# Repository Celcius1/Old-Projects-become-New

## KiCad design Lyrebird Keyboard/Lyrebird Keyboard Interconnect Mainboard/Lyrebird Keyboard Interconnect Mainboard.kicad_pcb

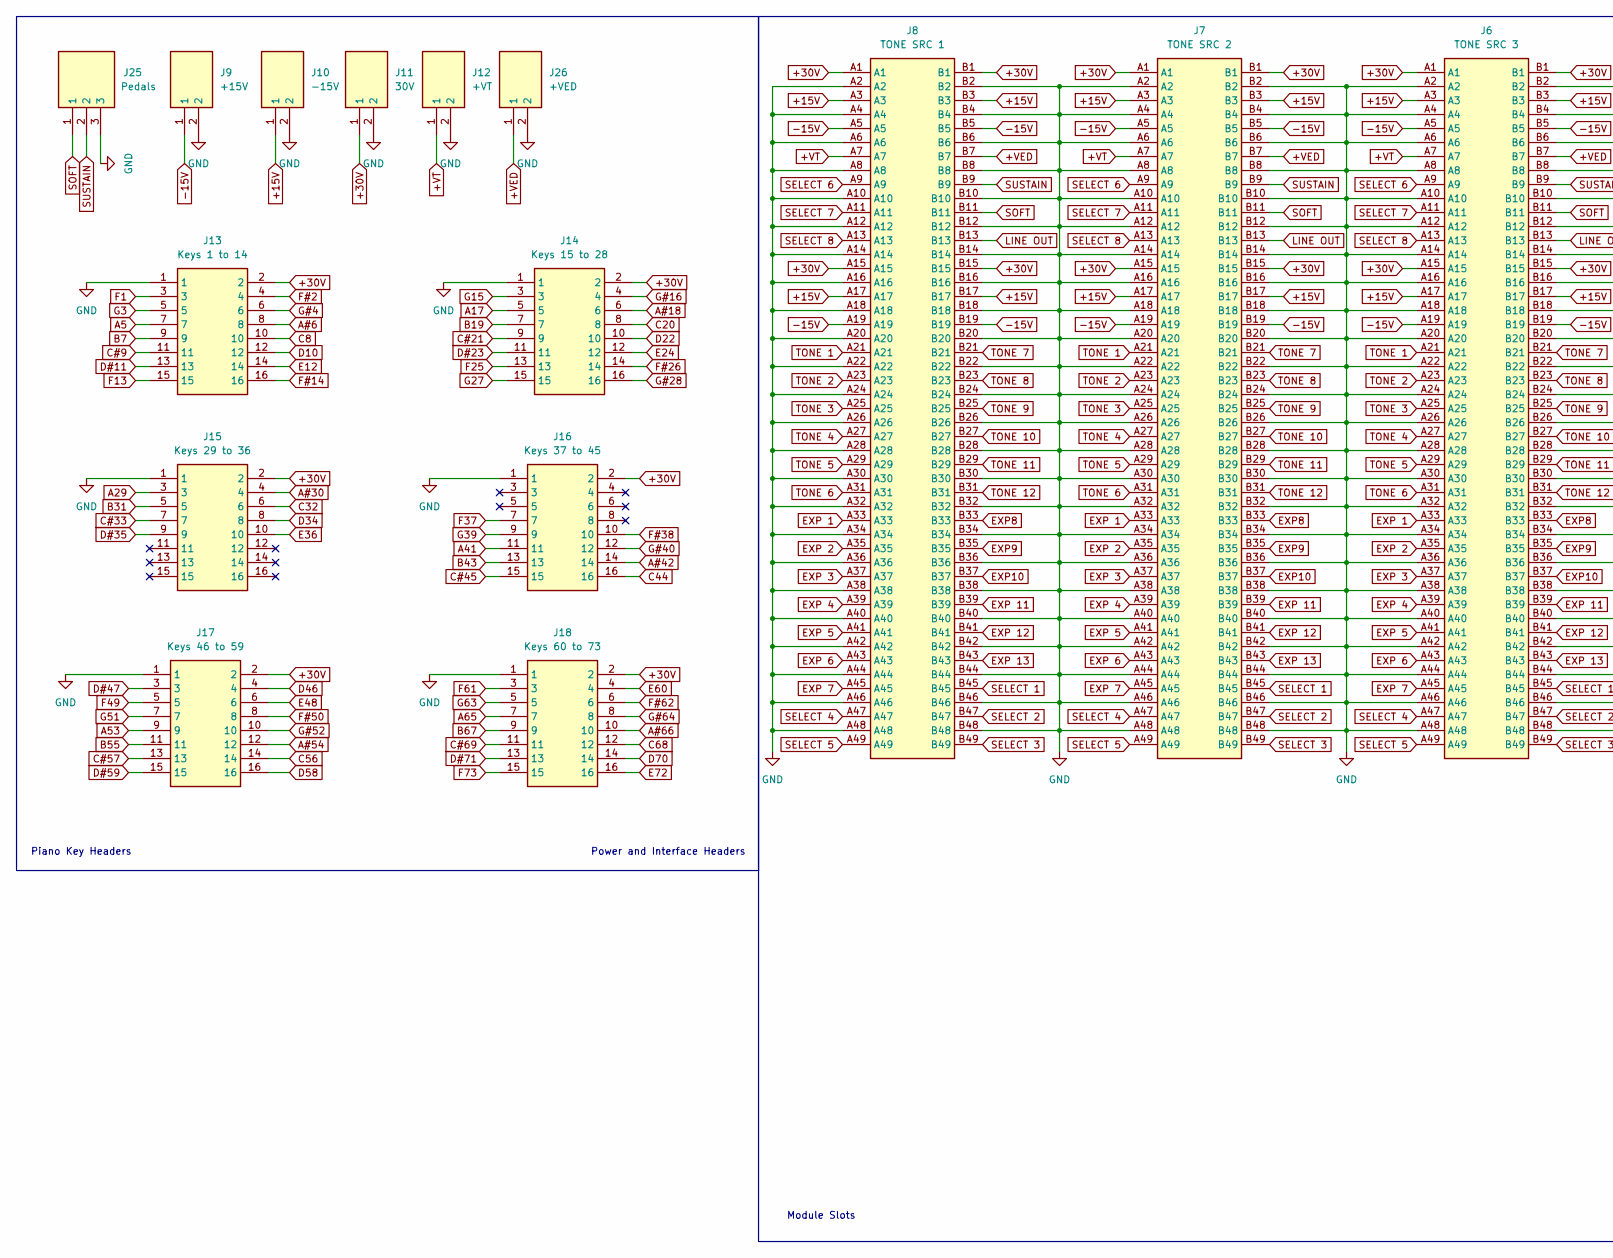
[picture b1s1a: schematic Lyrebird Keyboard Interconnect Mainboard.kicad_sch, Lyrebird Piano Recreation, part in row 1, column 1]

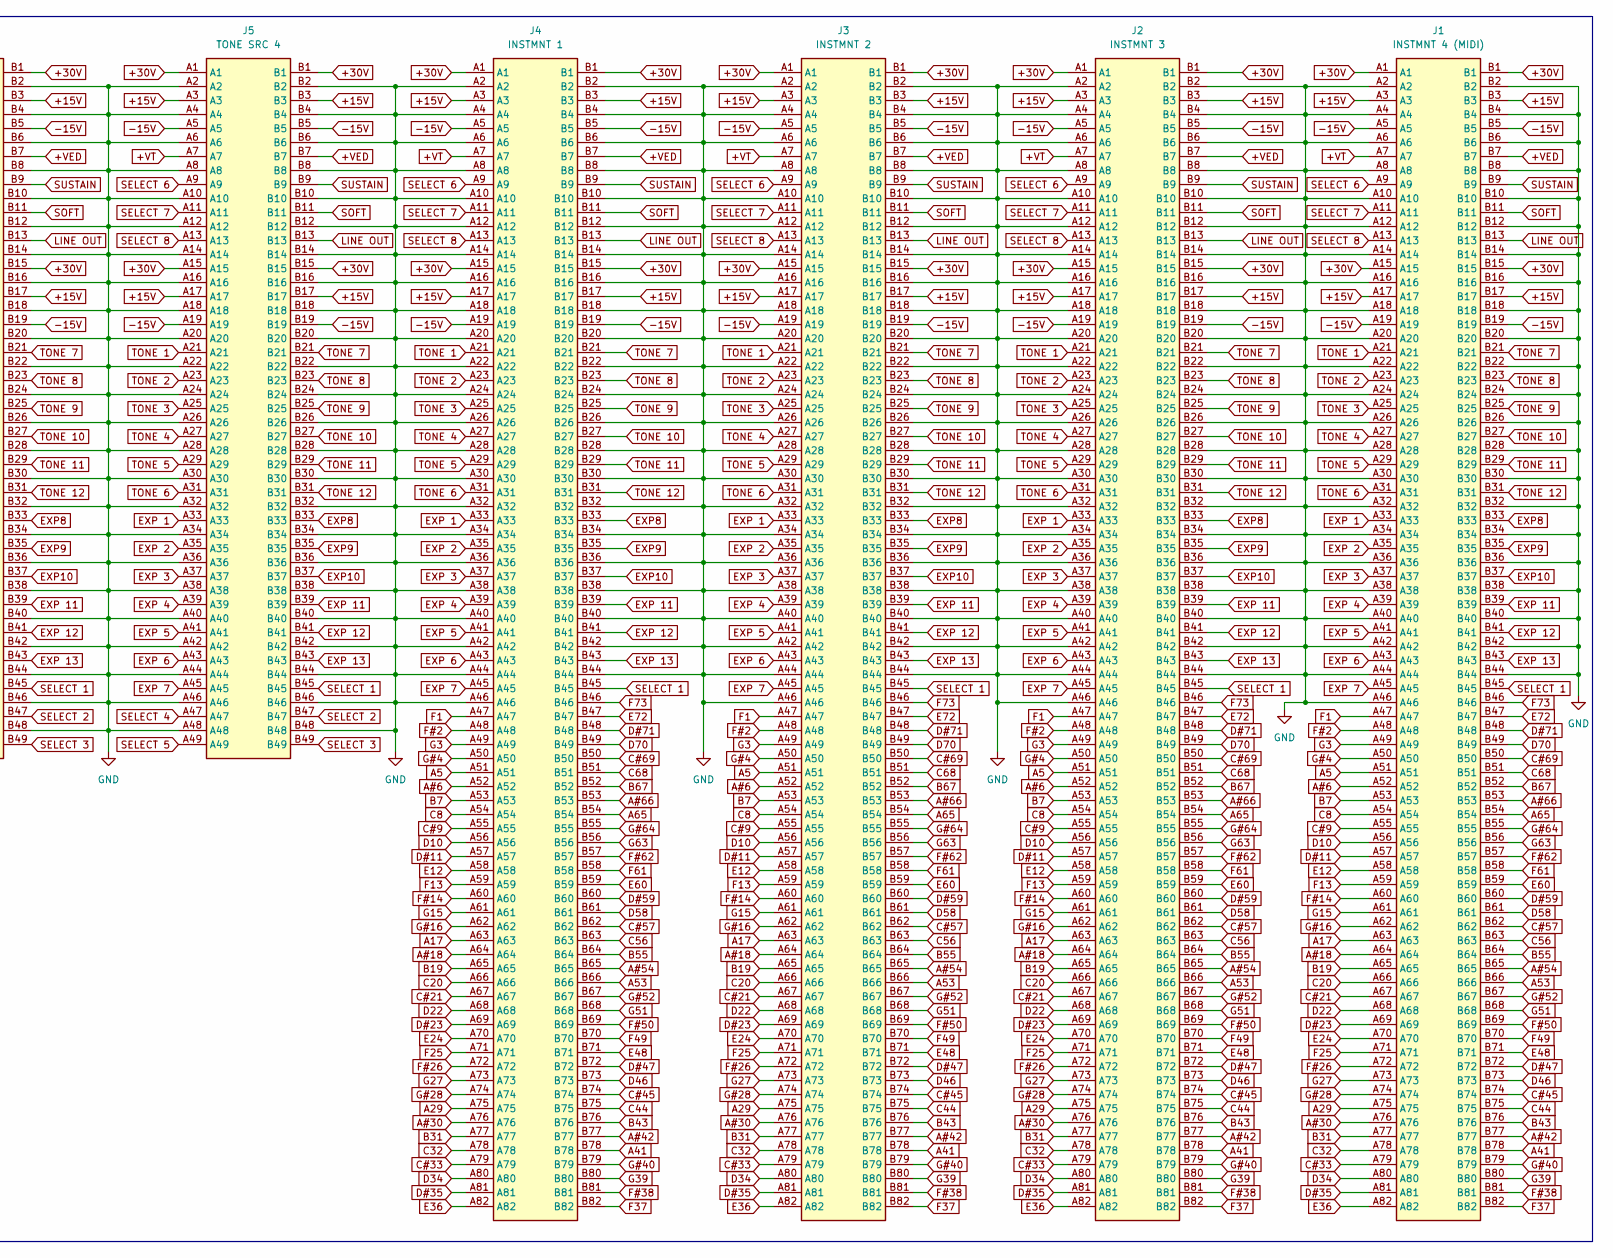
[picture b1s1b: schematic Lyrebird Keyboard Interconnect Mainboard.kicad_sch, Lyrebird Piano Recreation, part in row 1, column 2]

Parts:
J1: INSTMNT 4 (MIDI); 877159306; Manufacturer_Part_Number 87715-9306
J2: INSTMNT 3; 877159306; Manufacturer_Part_Number 87715-9306
J3: INSTMNT 2; 877159306; Manufacturer_Part_Number 87715-9306
J4: INSTMNT 1; 877159306; Manufacturer_Part_Number 87715-9306
J5: TONE SRC 4; 1001878410212TLF; Manufacturer_Part_Number 10018784-10212TLF
J6: TONE SRC 3; 1001878410212TLF; Manufacturer_Part_Number 10018784-10212TLF
J7: TONE SRC 2; 1001878410212TLF; Manufacturer_Part_Number 10018784-10212TLF
J8: TONE SRC 1; 1001878410212TLF; Manufacturer_Part_Number 10018784-10212TLF
J9: +15V; 17761192; Manufacturer_Part_Number 1776119-2
J10: -15V; 17761192; Manufacturer_Part_Number 1776119-2
J11: 30V; 17761192; Manufacturer_Part_Number 1776119-2
J12: +VT; 17761192; Manufacturer_Part_Number 1776119-2
J13: Keys 1 to 14; SHDR16W64P254_2X8_2798X910X910P; Manufacturer_Part_Number MC-254-16-00-ST-DIP
J14: Keys 15 to 28; SHDR16W64P254_2X8_2798X910X910P; Manufacturer_Part_Number MC-254-16-00-ST-DIP
J15: Keys 29 to 36; SHDR16W64P254_2X8_2798X910X910P; Manufacturer_Part_Number MC-254-16-00-ST-DIP
J16: Keys 37 to 45; SHDR16W64P254_2X8_2798X910X910P; Manufacturer_Part_Number MC-254-16-00-ST-DIP
J17: Keys 46 to 59; SHDR16W64P254_2X8_2798X910X910P; Manufacturer_Part_Number MC-254-16-00-ST-DIP
J18: Keys 60 to 73; SHDR16W64P254_2X8_2798X910X910P; Manufacturer_Part_Number MC-254-16-00-ST-DIP
J25: Pedals; CTB05083; Manufacturer_Part_Number CTB0508/3
J26: +VED; 17761192; Manufacturer_Part_Number 1776119-2

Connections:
+15V: J1.A3, J1.A17, J1.B3, J1.B17, J2.A3, J2.A17, J2.B3, J2.B17, J3.A3, J3.A17, J3.B3, J3.B17, J4.A3, J4.A17, J4.B3, J4.B17, J5.A3, J5.A17, J5.B3, J5.B17, J6.A3, J6.A17, J6.B3, J6.B17, J7.A3, J7.A17, J7.B3, J7.B17, J8.A3, J8.A17, J8.B3, J8.B17, J10.1
+30V: J1.A1, J1.A15, J1.B1, J1.B15, J2.A1, J2.A15, J2.B1, J2.B15, J3.A1, J3.A15, J3.B1, J3.B15, J4.A1, J4.A15, J4.B1, J4.B15, J5.A1, J5.A15, J5.B1, J5.B15, J6.A1, J6.A15, J6.B1, J6.B15, J7.A1, J7.A15, J7.B1, J7.B15, J8.A1, J8.A15, J8.B1, J8.B15, J11.1, J13.2, J14.2, J15.2, J16.2, J17.2, J18.2
+VED: J1.B7, J2.B7, J3.B7, J4.B7, J5.B7, J6.B7, J7.B7, J8.B7, J26.1
+VT: J1.A7, J2.A7, J3.A7, J4.A7, J5.A7, J6.A7, J7.A7, J8.A7, J12.1
-15V: J1.A5, J1.A19, J1.B5, J1.B19, J2.A5, J2.A19, J2.B5, J2.B19, J3.A5, J3.A19, J3.B5, J3.B19, J4.A5, J4.A19, J4.B5, J4.B19, J5.A5, J5.A19, J5.B5, J5.B19, J6.A5, J6.A19, J6.B5, J6.B19, J7.A5, J7.A19, J7.B5, J7.B19, J8.A5, J8.A19, J8.B5, J8.B19, J9.1
A5: J1.A51, J2.A51, J3.A51, J4.A51, J13.7
A17: J1.A63, J2.A63, J3.A63, J4.A63, J14.5
A29: J1.A75, J2.A75, J3.A75, J4.A75, J15.3
A41: J1.B78, J2.B78, J3.B78, J4.B78, J16.11
A53: J1.B66, J2.B66, J3.B66, J4.B66, J17.9
A65: J1.B54, J2.B54, J3.B54, J4.B54, J18.7
A#6: J1.A52, J2.A52, J3.A52, J4.A52, J13.8
A#18: J1.A64, J2.A64, J3.A64, J4.A64, J14.6
A#30: J1.A76, J2.A76, J3.A76, J4.A76, J15.4
A#42: J1.B77, J2.B77, J3.B77, J4.B77, J16.14
A#54: J1.B65, J2.B65, J3.B65, J4.B65, J17.12
A#66: J1.B53, J2.B53, J3.B53, J4.B53, J18.10
B7: J1.A53, J2.A53, J3.A53, J4.A53, J13.9
B19: J1.A65, J2.A65, J3.A65, J4.A65, J14.7
B31: J1.A77, J2.A77, J3.A77, J4.A77, J15.5
B43: J1.B76, J2.B76, J3.B76, J4.B76, J16.13
B55: J1.B64, J2.B64, J3.B64, J4.B64, J17.11
B67: J1.B52, J2.B52, J3.B52, J4.B52, J18.9
C8: J1.A54, J2.A54, J3.A54, J4.A54, J13.10
C20: J1.A66, J2.A66, J3.A66, J4.A66, J14.8
C32: J1.A78, J2.A78, J3.A78, J4.A78, J15.6
C44: J1.B75, J2.B75, J3.B75, J4.B75, J16.16
C56: J1.B63, J2.B63, J3.B63, J4.B63, J17.14
C68: J1.B51, J2.B51, J3.B51, J4.B51, J18.12
C#9: J1.A55, J2.A55, J3.A55, J4.A55, J13.11
C#21: J1.A67, J2.A67, J3.A67, J4.A67, J14.9
C#33: J1.A79, J2.A79, J3.A79, J4.A79, J15.7
C#45: J1.B74, J2.B74, J3.B74, J4.B74, J16.15
C#57: J1.B62, J2.B62, J3.B62, J4.B62, J17.13
C#69: J1.B50, J2.B50, J3.B50, J4.B50, J18.11
D10: J1.A56, J2.A56, J3.A56, J4.A56, J13.12
D22: J1.A68, J2.A68, J3.A68, J4.A68, J14.10
D34: J1.A80, J2.A80, J3.A80, J4.A80, J15.8
D46: J1.B73, J2.B73, J3.B73, J4.B73, J17.4
D58: J1.B61, J2.B61, J3.B61, J4.B61, J17.16
D70: J1.B49, J2.B49, J3.B49, J4.B49, J18.14
D#11: J1.A57, J2.A57, J3.A57, J4.A57, J13.13
D#23: J1.A69, J2.A69, J3.A69, J4.A69, J14.11
D#35: J1.A81, J2.A81, J3.A81, J4.A81, J15.9
D#47: J1.B72, J2.B72, J3.B72, J4.B72, J17.3
D#59: J1.B60, J2.B60, J3.B60, J4.B60, J17.15
D#71: J1.B48, J2.B48, J3.B48, J4.B48, J18.13
E12: J1.A58, J2.A58, J3.A58, J4.A58, J13.14
E24: J1.A70, J2.A70, J3.A70, J4.A70, J14.12
E36: J1.A82, J2.A82, J3.A82, J4.A82, J15.10
E48: J1.B71, J2.B71, J3.B71, J4.B71, J17.6
E60: J1.B59, J2.B59, J3.B59, J4.B59, J18.4
E72: J1.B47, J2.B47, J3.B47, J4.B47, J18.16
EXP8: J1.B33, J2.B33, J3.B33, J4.B33, J5.B33, J6.B33, J7.B33, J8.B33
EXP9: J1.B35, J2.B35, J3.B35, J4.B35, J5.B35, J6.B35, J7.B35, J8.B35
EXP10: J1.B37, J2.B37, J3.B37, J4.B37, J5.B37, J6.B37, J7.B37, J8.B37
EXP 1: J1.A33, J2.A33, J3.A33, J4.A33, J5.A33, J6.A33, J7.A33, J8.A33
EXP 2: J1.A35, J2.A35, J3.A35, J4.A35, J5.A35, J6.A35, J7.A35, J8.A35
EXP 3: J1.A37, J2.A37, J3.A37, J4.A37, J5.A37, J6.A37, J7.A37, J8.A37
EXP 4: J1.A39, J2.A39, J3.A39, J4.A39, J5.A39, J6.A39, J7.A39, J8.A39
EXP 5: J1.A41, J2.A41, J3.A41, J4.A41, J5.A41, J6.A41, J7.A41, J8.A41
EXP 6: J1.A43, J2.A43, J3.A43, J4.A43, J5.A43, J6.A43, J7.A43, J8.A43
EXP 7: J1.A45, J2.A45, J3.A45, J4.A45, J5.A45, J6.A45, J7.A45, J8.A45
EXP 11: J1.B39, J2.B39, J3.B39, J4.B39, J5.B39, J6.B39, J7.B39, J8.B39
EXP 12: J1.B41, J2.B41, J3.B41, J4.B41, J5.B41, J6.B41, J7.B41, J8.B41
EXP 13: J1.B43, J2.B43, J3.B43, J4.B43, J5.B43, J6.B43, J7.B43, J8.B43
F1: J1.A47, J2.A47, J3.A47, J4.A47, J13.3
F13: J1.A59, J2.A59, J3.A59, J4.A59, J13.15
F25: J1.A71, J2.A71, J3.A71, J4.A71, J14.13
F37: J1.B82, J2.B82, J3.B82, J4.B82, J16.7
F49: J1.B70, J2.B70, J3.B70, J4.B70, J17.5
F61: J1.B58, J2.B58, J3.B58, J4.B58, J18.3
F73: J1.B46, J2.B46, J3.B46, J4.B46, J18.15
F#2: J1.A48, J2.A48, J3.A48, J4.A48, J13.4
F#14: J1.A60, J2.A60, J3.A60, J4.A60, J13.16
F#26: J1.A72, J2.A72, J3.A72, J4.A72, J14.14
F#38: J1.B81, J2.B81, J3.B81, J4.B81, J16.10
F#50: J1.B69, J2.B69, J3.B69, J4.B69, J17.8
F#62: J1.B57, J2.B57, J3.B57, J4.B57, J18.6
G3: J1.A49, J2.A49, J3.A49, J4.A49, J13.5
G15: J1.A61, J2.A61, J3.A61, J4.A61, J14.3
G27: J1.A73, J2.A73, J3.A73, J4.A73, J14.15
G39: J1.B80, J2.B80, J3.B80, J4.B80, J16.9
G51: J1.B68, J2.B68, J3.B68, J4.B68, J17.7
G63: J1.B56, J2.B56, J3.B56, J4.B56, J18.5
G#4: J1.A50, J2.A50, J3.A50, J4.A50, J13.6
G#16: J1.A62, J2.A62, J3.A62, J4.A62, J14.4
G#28: J1.A74, J2.A74, J3.A74, J4.A74, J14.16
G#40: J1.B79, J2.B79, J3.B79, J4.B79, J16.12
G#52: J1.B67, J2.B67, J3.B67, J4.B67, J17.10
G#64: J1.B55, J2.B55, J3.B55, J4.B55, J18.8
GND: J1.A2, J1.A4, J1.A6, J1.A8, J1.A10, J1.A12, J1.A14, J1.A16, J1.A18, J1.A20, J1.A22, J1.A24, J1.A26, J1.A28, J1.A30, J1.A32, J1.A34, J1.A36, J1.A38, J1.A40, J1.A42, J1.A44, J1.A46, J1.B2, J1.B4, J1.B6, J1.B8, J1.B10, J1.B12, J1.B14, J1.B16, J1.B18, J1.B20, J1.B22, J1.B24, J1.B26, J1.B28, J1.B30, J1.B32, J1.B34, J1.B36, J1.B38, J1.B40, J1.B42, J1.B44, J2.A2, J2.A4, J2.A6, J2.A8, J2.A10, J2.A12, J2.A14, J2.A16, J2.A18, J2.A20, J2.A22, J2.A24, J2.A26, J2.A28, J2.A30, J2.A32, J2.A34, J2.A36, J2.A38, J2.A40, J2.A42, J2.A44, J2.A46, J2.B2, J2.B4, J2.B6, J2.B8, J2.B10, J2.B12, J2.B14, J2.B16, J2.B18, J2.B20, J2.B22, J2.B24, J2.B26, J2.B28, J2.B30, J2.B32, J2.B34, J2.B36, J2.B38, J2.B40, J2.B42, J2.B44, J3.A2, J3.A4, J3.A6, J3.A8, J3.A10, J3.A12, J3.A14, J3.A16, J3.A18, J3.A20, J3.A22, J3.A24, J3.A26, J3.A28, J3.A30, J3.A32, J3.A34, J3.A36, J3.A38, J3.A40, J3.A42, J3.A44, J3.A46, J3.B2, J3.B4, J3.B6, J3.B8, J3.B10, J3.B12, J3.B14, J3.B16, J3.B18, J3.B20, J3.B22, J3.B24, J3.B26, J3.B28, J3.B30, J3.B32, J3.B34, J3.B36, J3.B38, J3.B40, J3.B42, J3.B44, J4.A2, J4.A4, J4.A6, J4.A8, J4.A10, J4.A12, J4.A14, J4.A16, J4.A18, J4.A20, J4.A22, J4.A24, J4.A26, J4.A28, J4.A30, J4.A32, J4.A34, J4.A36, J4.A38, J4.A40, J4.A42, J4.A44, J4.A46, J4.B2, J4.B4, J4.B6, J4.B8, J4.B10, J4.B12, J4.B14, J4.B16, J4.B18, J4.B20, J4.B22, J4.B24, J4.B26, J4.B28, J4.B30, J4.B32, J4.B34, J4.B36, J4.B38, J4.B40, J4.B42, J4.B44, J5.A2, J5.A4, J5.A6, J5.A8, J5.A10, J5.A12, J5.A14, J5.A16, J5.A18, J5.A20, J5.A22, J5.A24, J5.A26, J5.A28, J5.A30, J5.A32, J5.A34, J5.A36, J5.A38, J5.A40, J5.A42, J5.A44, J5.A46, J5.A48, J5.B2, J5.B4, J5.B6, J5.B8, J5.B10, J5.B12, J5.B14, J5.B16, J5.B18, J5.B20, J5.B22, J5.B24, J5.B26, J5.B28, J5.B30, J5.B32, J5.B34, J5.B36, J5.B38, J5.B40, J5.B42, J5.B44, J5.B46, J5.B48, J6.A2, J6.A4, J6.A6, J6.A8, J6.A10, J6.A12, J6.A14, J6.A16, J6.A18, J6.A20, J6.A22, J6.A24, J6.A26, J6.A28, J6.A30, J6.A32, J6.A34, J6.A36, J6.A38, J6.A40, J6.A42, J6.A44, J6.A46, J6.A48, J6.B2, J6.B4, J6.B6, J6.B8, J6.B10, J6.B12, J6.B14, J6.B16, J6.B18, J6.B20, J6.B22, J6.B24, J6.B26, J6.B28, J6.B30, J6.B32, J6.B34, J6.B36, J6.B38, J6.B40, J6.B42, J6.B44, J6.B46, J6.B48, J7.A2, J7.A4, J7.A6, J7.A8, J7.A10, J7.A12, J7.A14, J7.A16, J7.A18, J7.A20, J7.A22, J7.A24, J7.A26, J7.A28, J7.A30, J7.A32, J7.A34, J7.A36, J7.A38, J7.A40, J7.A42, J7.A44, J7.A46, J7.A48, J7.B2, J7.B4, J7.B6, J7.B8, J7.B10, J7.B12, J7.B14, J7.B16, J7.B18, J7.B20, J7.B22, J7.B24, J7.B26, J7.B28, J7.B30, J7.B32, J7.B34, J7.B36, J7.B38, J7.B40, J7.B42, J7.B44, J7.B46, J7.B48, J8.A2, J8.A4, J8.A6, J8.A8, J8.A10, J8.A12, J8.A14, J8.A16, J8.A18, J8.A20, J8.A22, J8.A24, J8.A26, J8.A28, J8.A30, J8.A32, J8.A34, J8.A36, J8.A38, J8.A40, J8.A42, J8.A44, J8.A46, J8.A48, J8.B2, J8.B4, J8.B6, J8.B8, J8.B10, J8.B12, J8.B14, J8.B16, J8.B18, J8.B20, J8.B22, J8.B24, J8.B26, J8.B28, J8.B30, J8.B32, J8.B34, J8.B36, J8.B38, J8.B40, J8.B42, J8.B44, J8.B46, J8.B48, J9.2, J10.2, J11.2, J12.2, J13.1, J14.1, J15.1, J16.1, J17.1, J18.1, J25.3, J26.2
LINE OUT: J1.B13, J2.B13, J3.B13, J4.B13, J5.B13, J6.B13, J7.B13, J8.B13
SELECT 1: J1.B45, J2.B45, J3.B45, J4.B45, J5.B45, J6.B45, J7.B45, J8.B45
SELECT 2: J5.B47, J6.B47, J7.B47, J8.B47
SELECT 3: J5.B49, J6.B49, J7.B49, J8.B49
SELECT 4: J5.A47, J6.A47, J7.A47, J8.A47
SELECT 5: J5.A49, J6.A49, J7.A49, J8.A49
SELECT 6: J1.A9, J2.A9, J3.A9, J4.A9, J5.A9, J6.A9, J7.A9, J8.A9
SELECT 7: J1.A11, J2.A11, J3.A11, J4.A11, J5.A11, J6.A11, J7.A11, J8.A11
SELECT 8: J1.A13, J2.A13, J3.A13, J4.A13, J5.A13, J6.A13, J7.A13, J8.A13
SOFT: J1.B11, J2.B11, J3.B11, J4.B11, J5.B11, J6.B11, J7.B11, J8.B11, J25.1
SUSTAIN: J1.B9, J2.B9, J3.B9, J4.B9, J5.B9, J6.B9, J7.B9, J8.B9, J25.2
TONE 1: J1.A21, J2.A21, J3.A21, J4.A21, J5.A21, J6.A21, J7.A21, J8.A21
TONE 2: J1.A23, J2.A23, J3.A23, J4.A23, J5.A23, J6.A23, J7.A23, J8.A23
TONE 3: J1.A25, J2.A25, J3.A25, J4.A25, J5.A25, J6.A25, J7.A25, J8.A25
TONE 4: J1.A27, J2.A27, J3.A27, J4.A27, J5.A27, J6.A27, J7.A27, J8.A27
TONE 5: J1.A29, J2.A29, J3.A29, J4.A29, J5.A29, J6.A29, J7.A29, J8.A29
TONE 6: J1.A31, J2.A31, J3.A31, J4.A31, J5.A31, J6.A31, J7.A31, J8.A31
TONE 7: J1.B21, J2.B21, J3.B21, J4.B21, J5.B21, J6.B21, J7.B21, J8.B21
TONE 8: J1.B23, J2.B23, J3.B23, J4.B23, J5.B23, J6.B23, J7.B23, J8.B23
TONE 9: J1.B25, J2.B25, J3.B25, J4.B25, J5.B25, J6.B25, J7.B25, J8.B25
TONE 10: J1.B27, J2.B27, J3.B27, J4.B27, J5.B27, J6.B27, J7.B27, J8.B27
TONE 11: J1.B29, J2.B29, J3.B29, J4.B29, J5.B29, J6.B29, J7.B29, J8.B29
TONE 12: J1.B31, J2.B31, J3.B31, J4.B31, J5.B31, J6.B31, J7.B31, J8.B31

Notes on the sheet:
Piano Key Headers
Power and Interface Headers
Module Slots

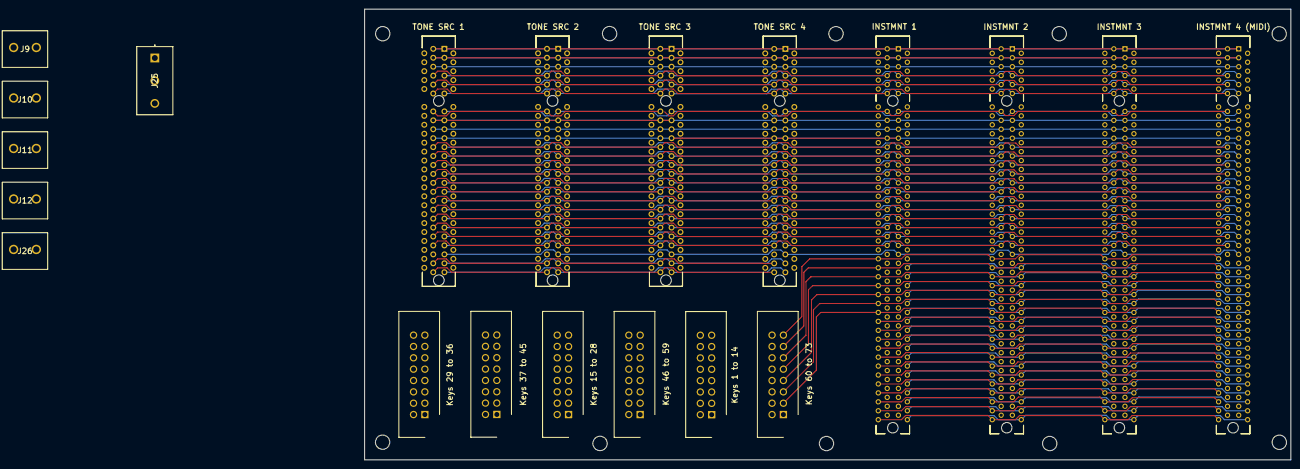
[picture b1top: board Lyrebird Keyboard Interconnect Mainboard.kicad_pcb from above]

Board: 4 copper layers, 207.3 x 100.9 mm, 20 parts (0 on the bottom side), 115 nets.

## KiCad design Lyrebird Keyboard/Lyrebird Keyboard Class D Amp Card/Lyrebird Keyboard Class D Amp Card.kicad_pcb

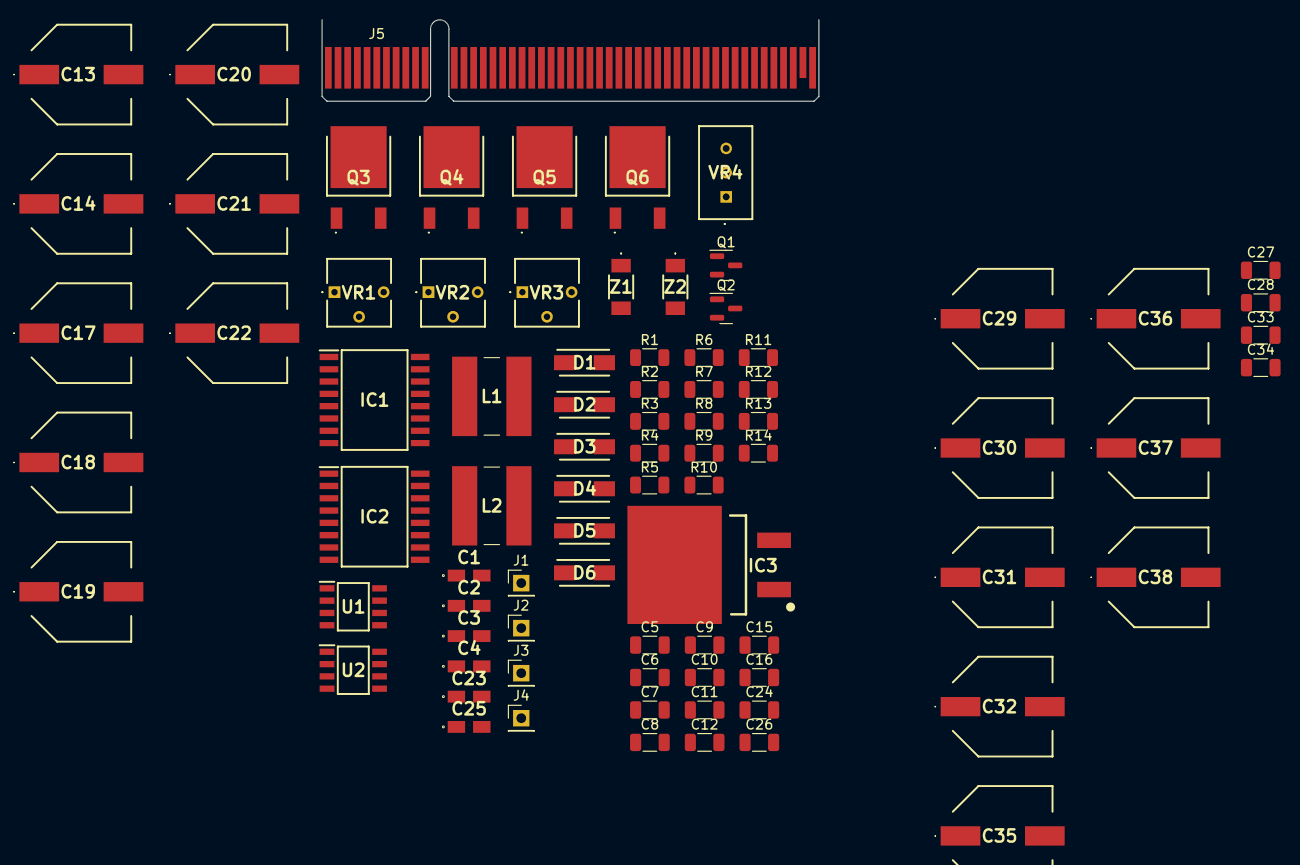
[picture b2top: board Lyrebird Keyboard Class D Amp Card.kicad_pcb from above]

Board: 2 copper layers, 82 parts (0 on the bottom side), 36 nets, no tracks yet.

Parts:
C1, C2, C3, C4, C23, C25: T491A225K016AT; T491A
C5, C6, C11, C12, C28, C34: 220nF; C_1206_3216Metric
C7, C8: 22uF; C_1206_3216Metric
C9, C10, C27, C33: 100nF; C_1206_3216Metric
C13, C14, C17, C18, C19, C20, C21, C22, C29, C30, C31, C32, C35, C36, C37, C38: EEEFK1H221P; EEE0JA152UAP
C15: 390nF; C_1206_3216Metric
C16: 5.6uF; C_1206_3216Metric
C24: 68nF; C_1206_3216Metric
C26: 1nF; C_1206_3216Metric
D1, D2, D3, D4, D5, D6: US1M-E3_5AT; DIOM5127X229N
IC1, IC2: IR2113SPBF; SOIC127P1032X265-16N
IC3: L7805ACD2T-TR; D2PAK-STB35NF10T4
J1: Bias Test Point 1; PinHeader_1x01_P2.54mm_Vertical
J2: Bias Test Point 2; PinHeader_1x01_P2.54mm_Vertical
J3: Square Test; PinHeader_1x01_P2.54mm_Vertical
J4: Triangle Test; PinHeader_1x01_P2.54mm_Vertical
J5: Edge Connector; BUS_PCIexpress_x8
L1, L2: SRN8040-220M; SRN8040220M
Q1, Q2: BC848; SOT-23
Q3, Q4, Q5, Q6: IRFR2905ZTRPBF
R1, R2, R3, R4, R5, R6, R11: 10k; R_1206_3216Metric
R7, R8, R9, R10: 10R; R_1206_3216Metric
R12, R13: 100k; R_1206_3216Metric
R14: 5k1; R_1206_3216Metric
U1: SOIC127P600X175-8N
U2: LM358; SOIC127P600X175-8N
VR1, VR2, VR3: T73YP103KT20
VR4: CT-9EW104; CT9EW104
Z1, Z2: PDZVTFTR4.7B; PDZVTFTR47B

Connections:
+5V: C1.1 (+), C2.1 (+), C3.1 (+), C4.1 (+), C23.1 (+), C25.1 (+), IC1.11 (VDD), IC2.11 (VDD), IC3.3 (OUTPUT), R3.1, R4.1, R5.2, R6.2, U1.8 (Vdd), U2.8 (V+), VR2.3 (CW), VR3.3 (CW)
+15V: C9.2, C10.2, C11.2, C12.2, C13.1 (+), C14.1 (+), C17.1 (+), C18.1 (+), C19.1 (+), C20.1 (+), C21.1 (+), C22.1 (+), D1.2 (A), D2.2 (A), IC1.3 (VCC), IC2.3 (VCC), IC3.1 (INPUT), J5.A3, J5.A17, J5.B3, J5.B17, Q3.2 (D), Q5.2 (D)
-15V: C27.1, C28.1, C29.2 (-), C30.2 (-), C31.2 (-), C32.2 (-), C33.1, C34.1, C35.2 (-), C36.2 (-), C37.2 (-), C38.2 (-), J5.A5, J5.A19, J5.B5, J5.B19, Q4.3 (S), Q6.3 (S)
AMP OUT: C15.2, L1.2
GND: C1.2 (-), C2.2 (-), C3.2 (-), C4.2 (-), C9.1, C10.1, C11.1, C12.1, C13.2 (-), C14.2 (-), C15.1, C16.1, C17.2 (-), C18.2 (-), C19.2 (-), C20.2 (-), C21.2 (-), C22.2 (-), C23.2 (-), C24.1, C25.2 (-), C27.2, C28.2, C29.1 (+), C30.1 (+), C31.1 (+), C32.1 (+), C33.2, C34.2, C35.1 (+), C36.1 (+), C37.1 (+), C38.1 (+), IC1.13 (SD), IC2.13 (SD), IC3.4 (GND), J5.A2, J5.A4, J5.A6, J5.A8, J5.A10, J5.A12, J5.A14, J5.A16, J5.A18, J5.A20, J5.A32, J5.A34, J5.A36, J5.A38, J5.A40, J5.A42, J5.A44, J5.A46, J5.A48, J5.B2, J5.B4, J5.B6, J5.B8, J5.B10, J5.B12, J5.B14, J5.B16, J5.B18, J5.B20, J5.B32, J5.B34, J5.B36, J5.B38, J5.B40, J5.B42, J5.B44, J5.B46, J5.B48, Q1.2 (E), Q2.2 (E), U1.4 (Vss), U2.2 (-), U2.4 (V-), U2.5 (+), VR2.1 (CCW), VR3.1 (CCW), Z1.2 (A)
HIN1: IC1.12 (HIN), R1.1, R6.1, U1.7
HIN2: IC2.12 (HIN), R2.1, R5.1, U1.1
HO1: D5.1 (K), IC1.8 (HO), R9.2
HO2: D3.1 (K), IC2.8 (HO), R7.2
LINE INV: IC2.14 (LIN), Q2.3 (C), R4.2
LINE OUT: J5.B13, VR1.3 (CW)
LO1: D6.1 (K), IC1.1 (LO), R10.2
LO2: D4.1 (K), IC2.1 (LO), R8.2
unnamed: D3.2 (A), Q3.1 (G), R7.1
unnamed: D4.2 (A), Q4.1 (G), R8.1
unnamed: D5.2 (A), Q5.1 (G), R9.1
unnamed: D6.2 (A), Q6.1 (G), R10.1
unnamed: J1.1, U1.2 (-), VR1.1 (CCW), VR2.2 (WIPER)
unnamed: J3.1, R13.1, R14.2, VR4.1 (CCW), Z2.2 (A)
unnamed: Q1.1 (B), R1.2
unnamed: Q2.1 (B), R2.2
unnamed: R14.1, U2.1
unnamed: C24.2, R11.1, U1.6 (-)
unnamed: R12.2, R13.2, U2.3 (+)
unnamed: C26.1, U2.6 (-), VR4.2 (WIPER)
unnamed: Z1.1 (K), Z2.1 (K)
SUB IN: J2.1, R11.2, VR1.2 (WIPER), VR3.2 (WIPER)
SUB INV: IC1.14 (LIN), Q1.3 (C), R3.2
SUBWOOFER: C16.2, L2.2
TRI WAVE OUT: C26.2, J4.1, R12.1, U1.3 (+), U1.5 (+), U2.7
VB1: C6.1, C8.2, D2.1 (K), IC1.7 (VB)
VB2: C5.1, C7.2, D1.1 (K), IC2.7 (VB)
VS1: C6.2, C8.1, IC1.6 (VS), L2.1, Q5.3 (S), Q6.2 (D)
VS2: C5.2, C7.1, IC2.6 (VS), L1.1, Q3.3 (S), Q4.2 (D)
VSS1: IC1.2 (COM), IC1.15 (VSS)
VSS2: IC2.2 (COM), IC2.15 (VSS)

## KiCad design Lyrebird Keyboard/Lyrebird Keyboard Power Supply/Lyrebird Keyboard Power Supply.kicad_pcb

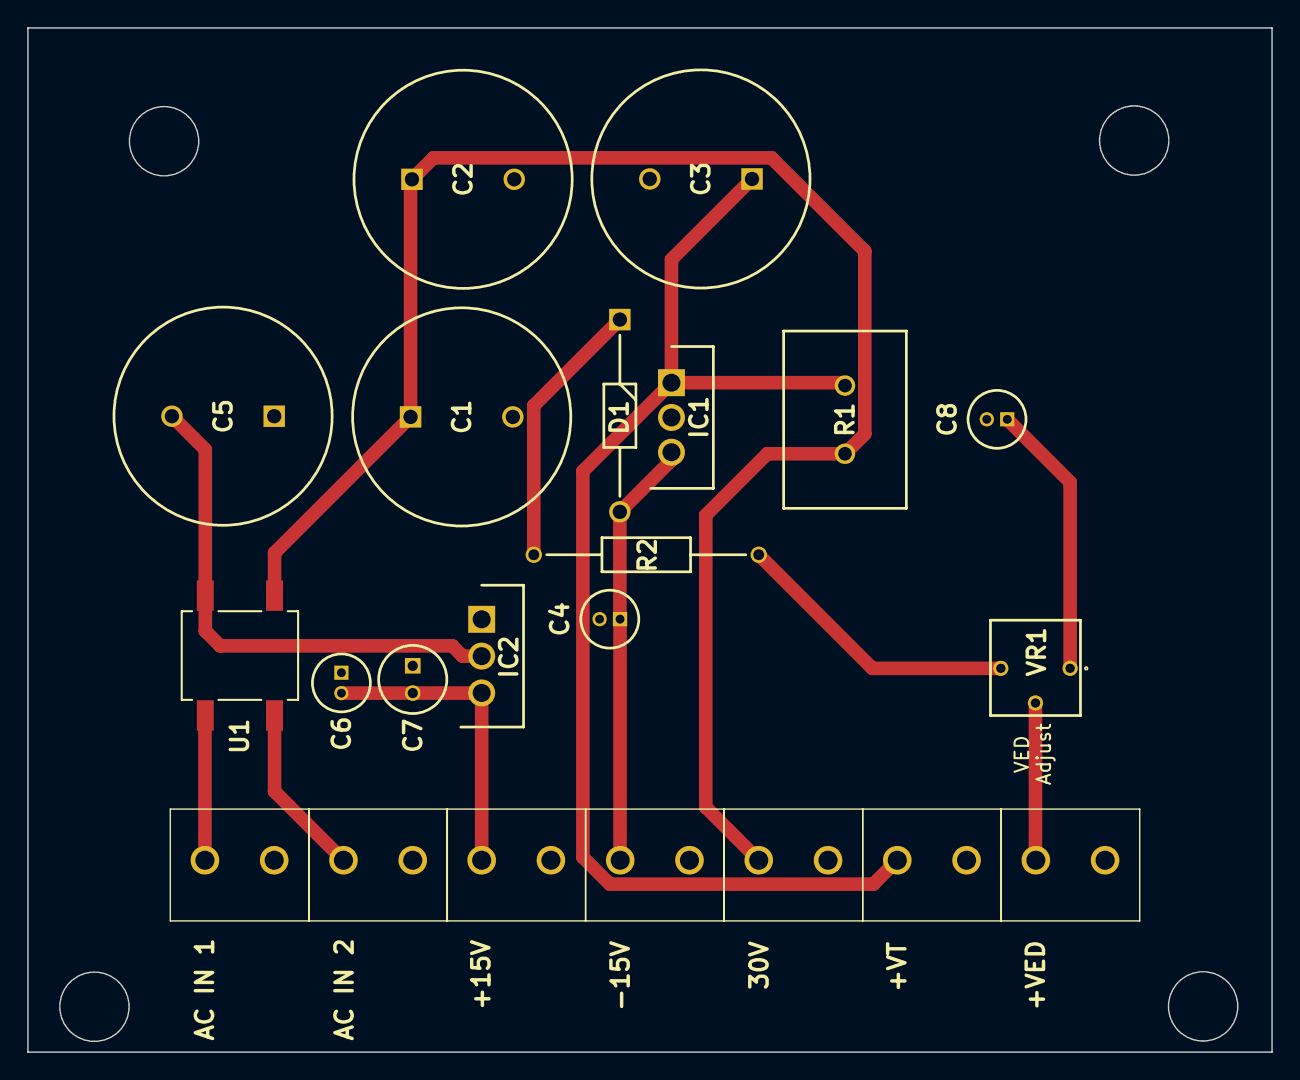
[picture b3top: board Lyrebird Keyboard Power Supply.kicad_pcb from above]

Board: 2 copper layers, 91.2 x 75.1 mm, 22 parts (0 on the bottom side), 12 nets.

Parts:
C1, C2, C3, C5: ECA1HHG222; CAPPRD750W85D1600H3350
C4, C6, C8: MCMHR50V104M4X7; CAPPRD150W47D425H800
C7: EEUFC1H4R7; CAPPRD200W55D500H1250
D1: 1N4002G; DIOAD1405W86L465D235
IC1: L78S15CV; TO255P460X1020X2008-3P
IC2: L7915CV; TO270P460X1020X2008-3P
J1: AC IN 1; 17761192
J2: AC IN 2; 17761192
J3: +15V; 17761192
J4: -15V; 17761192
J5: 30V; 17761192
J6: +VT; 17761192
J7: +VED; 17761192
R1: SQMR54K7J
R2: MRS25000C1801FCT00; RESAD1650W60L650D250
U1: DF06S; SOT508P985X260-4N
VR1: 3362P-1-102LF; 3362P_1

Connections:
+15V: C4.1 (+), D1.2 (A), IC1.3 (OUTPUT), J4.1
+30V: C1.1 (+), C2.1 (+), J5.1, R1.1, U1.1 (OUT+)
+VED: J7.1, VR1.2 (WIPER)
+VT: C3.1 (+), IC1.1 (INPUT), J6.1, R1.2
-15V: C6.2 (-), C7.2 (-), IC2.3 (OUT), J3.1
AC1: J1.1, U1.3 (AC)
AC2: J2.1, U1.4 (AC_2)
GND: C1.2 (-), C2.2 (-), C3.2 (-), C4.2 (-), C5.1 (+), C6.1 (+), C7.1 (+), C8.2 (-), IC1.2 (GROUND), IC2.1 (GND), J1.2, J2.2, J3.2, J4.2, J5.2, J6.2, J7.2
unnamed: C5.2 (-), IC2.2 (IN), U1.2 (OUT-)
unnamed: C8.1 (+), VR1.1 (CCW)
unnamed: D1.1 (K), R2.1
unnamed: R2.2, VR1.3 (CW)

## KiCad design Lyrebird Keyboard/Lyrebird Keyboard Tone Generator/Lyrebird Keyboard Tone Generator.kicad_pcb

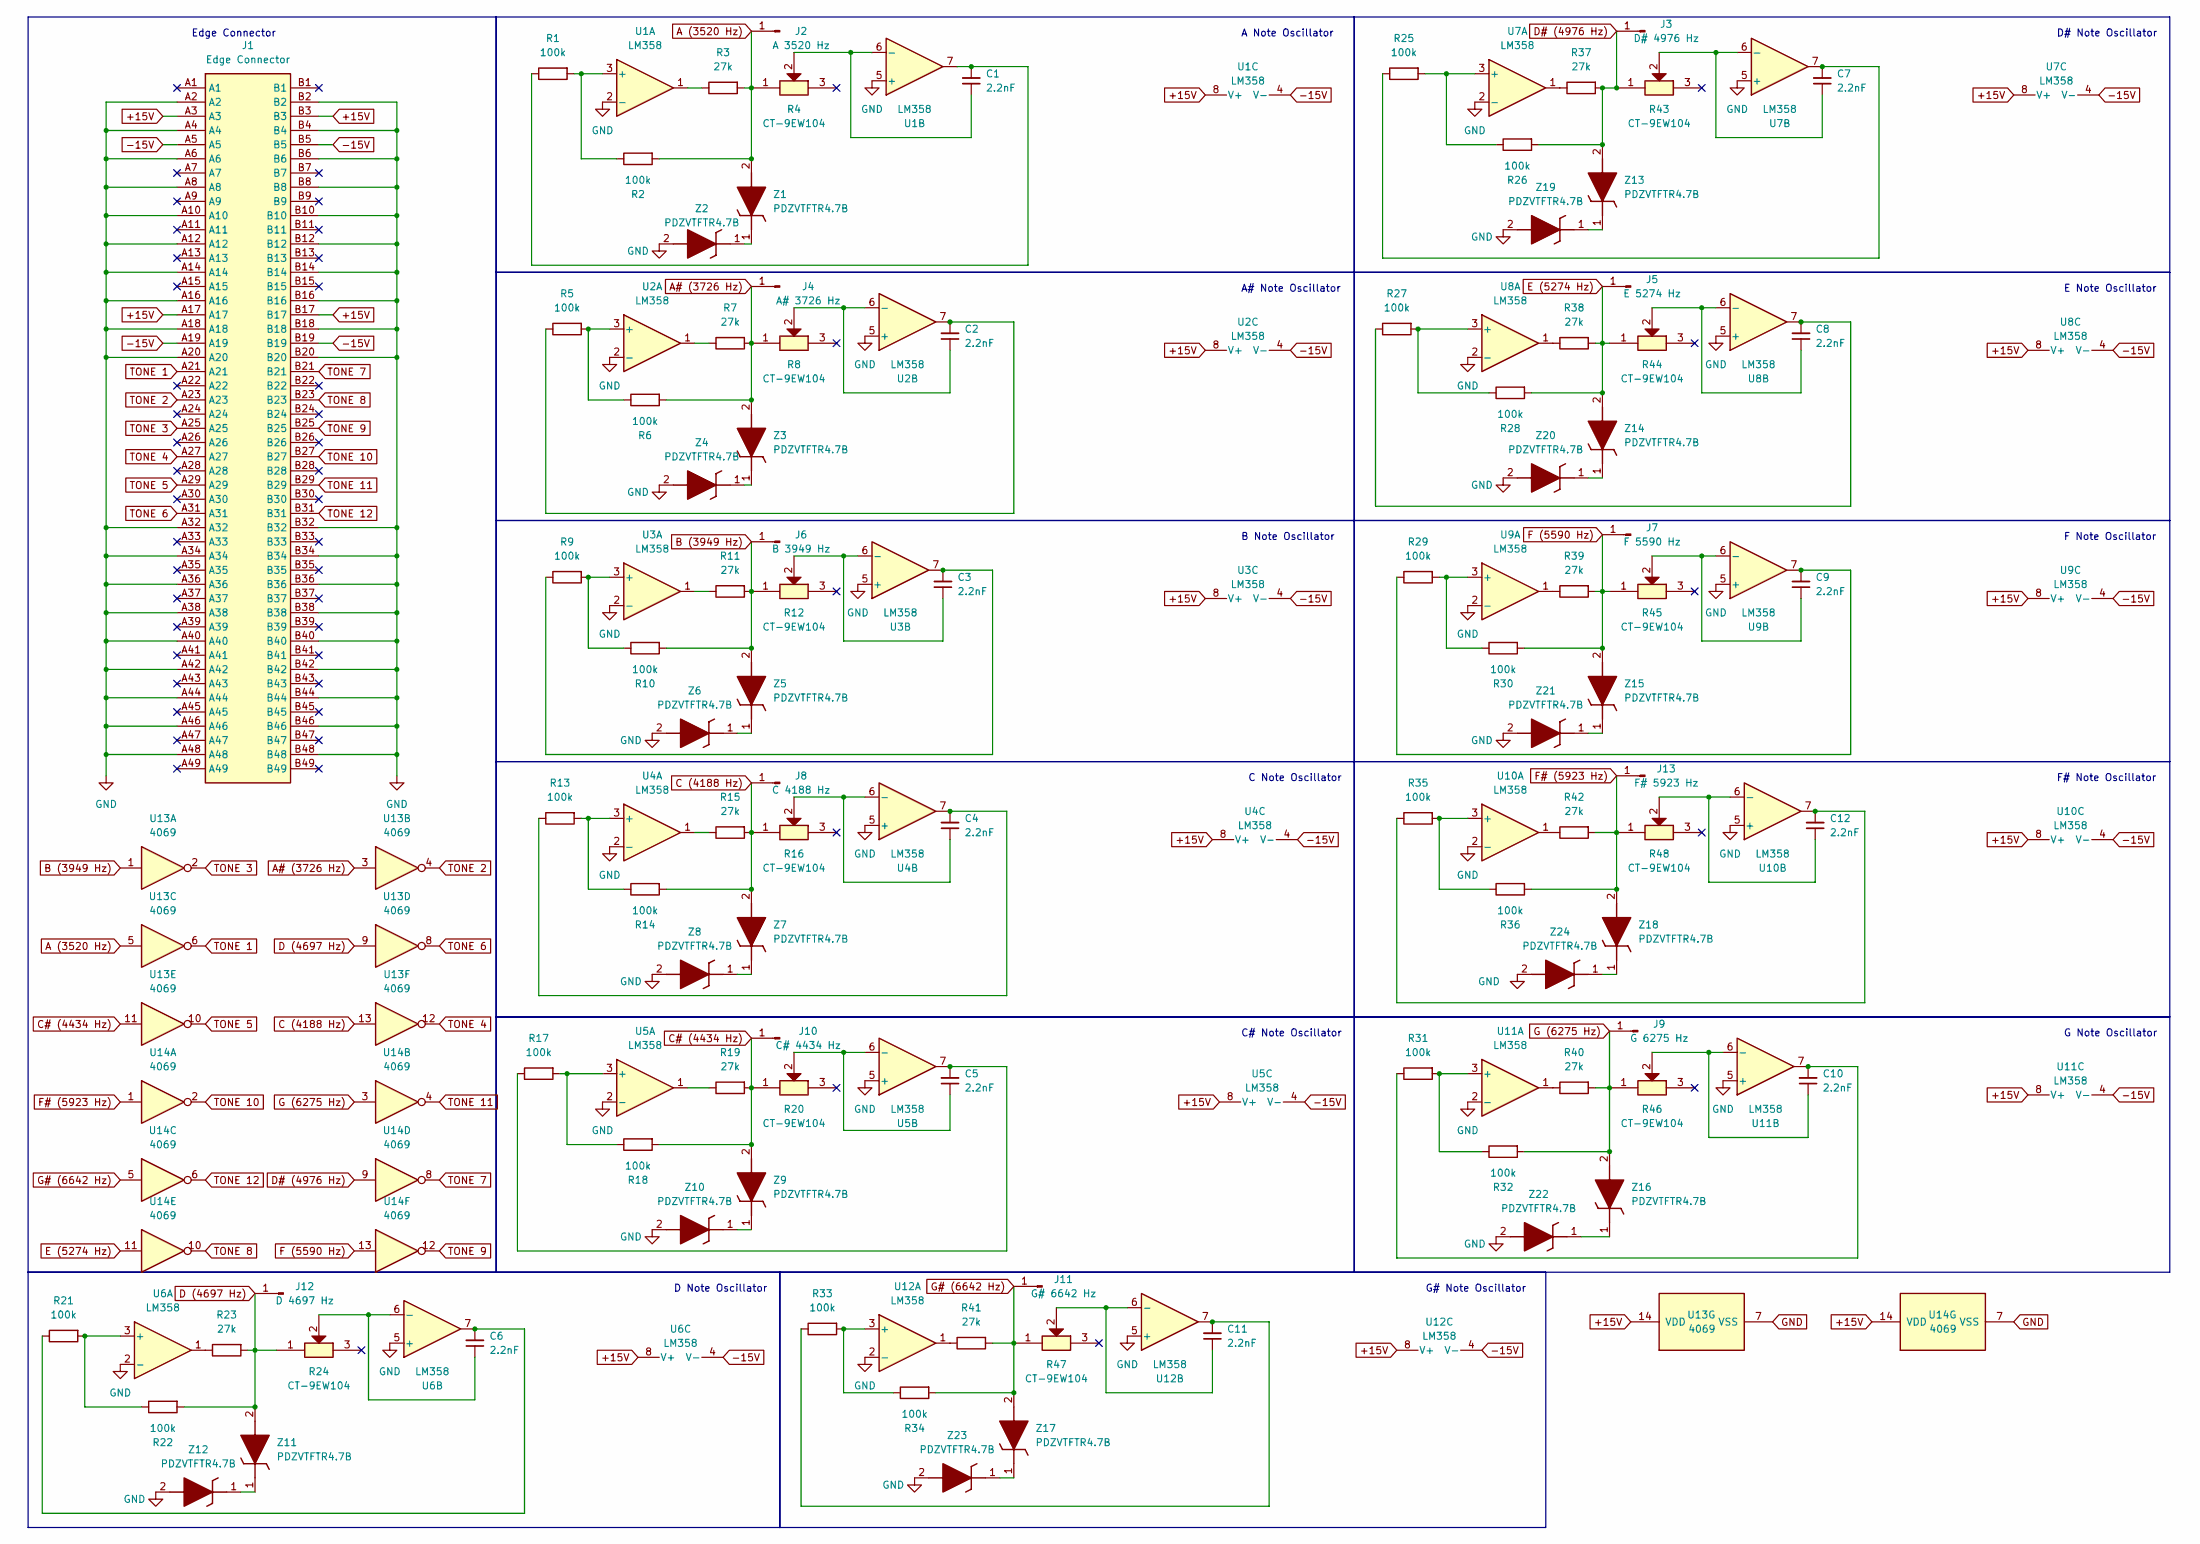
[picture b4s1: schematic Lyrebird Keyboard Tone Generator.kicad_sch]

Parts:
C1, C2, C3, C4, C5, C6, C7, C8, C9, C10, C11, C12: 2.2nF; C_1206_3216Metric
J1: Edge Connector; BUS_PCIexpress_x8; Manufacturer_Part_Number PCIE-098-02-F-D-TH
J2: A 3520 Hz; PinHeader_1x01_P2.54mm_Vertical
J3: D# 4976 Hz; PinHeader_1x01_P2.54mm_Vertical
J4: A# 3726 Hz; PinHeader_1x01_P2.54mm_Vertical
J5: E 5274 Hz; PinHeader_1x01_P2.54mm_Vertical
J6: B 3949 Hz; PinHeader_1x01_P2.54mm_Vertical
J7: F 5590 Hz; PinHeader_1x01_P2.54mm_Vertical
J8: C 4188 Hz; PinHeader_1x01_P2.54mm_Vertical
J9: G 6275 Hz; PinHeader_1x01_P2.54mm_Vertical
J10: C# 4434 Hz; PinHeader_1x01_P2.54mm_Vertical
J11: G# 6642 Hz; PinHeader_1x01_P2.54mm_Vertical
J12: D 4697 Hz; PinHeader_1x01_P2.54mm_Vertical
J13: F# 5923 Hz; PinHeader_1x01_P2.54mm_Vertical
R1, R2, R5, R6, R9, R10, R13, R14, R17, R18, R21, R22, R25, R26, R27, R28, R29, R30, R31, R32, R33, R34, R35, R36: 100k; R_1206_3216Metric
R3, R7, R11, R15, R19, R23, R37, R38, R39, R40, R41, R42: 27k; R_1206_3216Metric
R4, R8, R12, R16, R20, R24, R43, R44, R45, R46, R47, R48: CT-9EW104; CT9EW104; Manufacturer_Part_Number CT-9EW104
U1, U2, U3, U4, U5, U6, U7, U8, U9, U10, U11, U12: LM358; SOIC127P600X175-8N
U13, U14: 4069; SOIC127P600X175-14N
Z1, Z2, Z3, Z4, Z5, Z6, Z7, Z8, Z9, Z10, Z11, Z12, Z13, Z14, Z15, Z16, Z17, Z18, Z19, Z20, Z21, Z22, Z23, Z24: PDZVTFTR4.7B; PDZVTFTR47B; Manufacturer_Part_Number PDZVTFTR4.7B

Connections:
+15V: J1.A3, J1.A17, J1.B3, J1.B17, U1.8 (V+), U2.8 (V+), U3.8 (V+), U4.8 (V+), U5.8 (V+), U6.8 (V+), U7.8 (V+), U8.8 (V+), U9.8 (V+), U10.8 (V+), U11.8 (V+), U12.8 (V+), U13.14 (VDD), U14.14 (VDD)
-15V: J1.A5, J1.A19, J1.B5, J1.B19, U1.4 (V-), U2.4 (V-), U3.4 (V-), U4.4 (V-), U5.4 (V-), U6.4 (V-), U7.4 (V-), U8.4 (V-), U9.4 (V-), U10.4 (V-), U11.4 (V-), U12.4 (V-)
A (3520 Hz): J2.1, R2.2, R3.2, R4.1, U13.5, Z1.2 (A)
A# (3726 Hz): J4.1, R6.2, R7.2, R8.1, U13.3, Z3.2 (A)
B (3949 Hz): J6.1, R10.2, R11.2, R12.1, U13.1, Z5.2 (A)
C (4188 Hz): J8.1, R14.2, R15.2, R16.1, U13.13, Z7.2 (A)
C# (4434 Hz): J10.1, R18.2, R19.2, R20.1, U13.11, Z9.2 (A)
D (4697 Hz): J12.1, R22.2, R23.2, R24.1, U13.9, Z11.2 (A)
D# (4976 Hz): J3.1, R26.2, R37.2, R43.1, U14.9, Z13.2 (A)
E (5274 Hz): J5.1, R28.2, R38.2, R44.1, U14.11, Z14.2 (A)
F (5590 Hz): J7.1, R30.2, R39.2, R45.1, U14.13, Z15.2 (A)
F# (5923 Hz): J13.1, R36.2, R42.2, R48.1, U14.1, Z18.2 (A)
G (6275 Hz): J9.1, R32.2, R40.2, R46.1, U14.3, Z16.2 (A)
G# (6642 Hz): J11.1, R34.2, R41.2, R47.1, U14.5, Z17.2 (A)
GND: J1.A2, J1.A4, J1.A6, J1.A8, J1.A10, J1.A12, J1.A14, J1.A16, J1.A18, J1.A20, J1.A32, J1.A34, J1.A36, J1.A38, J1.A40, J1.A42, J1.A44, J1.A46, J1.A48, J1.B2, J1.B4, J1.B6, J1.B8, J1.B10, J1.B12, J1.B14, J1.B16, J1.B18, J1.B20, J1.B32, J1.B34, J1.B36, J1.B38, J1.B40, J1.B42, J1.B44, J1.B46, J1.B48, U1.2 (-), U1.5 (+), U2.2 (-), U2.5 (+), U3.2 (-), U3.5 (+), U4.2 (-), U4.5 (+), U5.2 (-), U5.5 (+), U6.2 (-), U6.5 (+), U7.2 (-), U7.5 (+), U8.2 (-), U8.5 (+), U9.2 (-), U9.5 (+), U10.2 (-), U10.5 (+), U11.2 (-), U11.5 (+), U12.2 (-), U12.5 (+), U13.7 (VSS), U14.7 (VSS), Z2.2 (A), Z4.2 (A), Z6.2 (A), Z8.2 (A), Z10.2 (A), Z12.2 (A), Z19.2 (A), Z20.2 (A), Z21.2 (A), Z22.2 (A), Z23.2 (A), Z24.2 (A)
unnamed: C1.2, R1.1, U1.7
unnamed: C2.2, R5.1, U2.7
unnamed: C3.2, R9.1, U3.7
unnamed: C4.2, R13.1, U4.7
unnamed: C5.2, R17.1, U5.7
unnamed: C6.2, R21.1, U6.7
unnamed: C7.2, R25.1, U7.7
unnamed: C8.2, R27.1, U8.7
unnamed: C9.2, R29.1, U9.7
unnamed: C10.2, R31.1, U11.7
unnamed: C11.2, R33.1, U12.7
unnamed: C12.2, R35.1, U10.7
unnamed: R3.1, U1.1
unnamed: R7.1, U2.1
unnamed: R11.1, U3.1
unnamed: R15.1, U4.1
unnamed: R19.1, U5.1
unnamed: R23.1, U6.1
unnamed: R37.1, U7.1
unnamed: R38.1, U8.1
unnamed: R39.1, U9.1
unnamed: R40.1, U11.1
unnamed: R41.1, U12.1
unnamed: R42.1, U10.1
unnamed: R1.2, R2.1, U1.3 (+)
unnamed: C1.1, R4.2, U1.6 (-)
unnamed: R5.2, R6.1, U2.3 (+)
unnamed: C2.1, R8.2, U2.6 (-)
unnamed: R9.2, R10.1, U3.3 (+)
unnamed: C3.1, R12.2, U3.6 (-)
unnamed: R13.2, R14.1, U4.3 (+)
unnamed: C4.1, R16.2, U4.6 (-)
unnamed: R17.2, R18.1, U5.3 (+)
unnamed: C5.1, R20.2, U5.6 (-)
unnamed: R21.2, R22.1, U6.3 (+)
unnamed: C6.1, R24.2, U6.6 (-)
unnamed: R25.2, R26.1, U7.3 (+)
unnamed: C7.1, R43.2, U7.6 (-)
unnamed: R27.2, R28.1, U8.3 (+)
unnamed: C8.1, R44.2, U8.6 (-)
unnamed: R29.2, R30.1, U9.3 (+)
unnamed: C9.1, R45.2, U9.6 (-)
unnamed: R35.2, R36.1, U10.3 (+)
unnamed: C12.1, R48.2, U10.6 (-)
unnamed: R31.2, R32.1, U11.3 (+)
unnamed: C10.1, R46.2, U11.6 (-)
unnamed: R33.2, R34.1, U12.3 (+)
unnamed: C11.1, R47.2, U12.6 (-)
unnamed: Z1.1 (K), Z2.1 (K)
unnamed: Z3.1 (K), Z4.1 (K)
unnamed: Z5.1 (K), Z6.1 (K)
unnamed: Z7.1 (K), Z8.1 (K)
unnamed: Z9.1 (K), Z10.1 (K)
unnamed: Z11.1 (K), Z12.1 (K)
unnamed: Z13.1 (K), Z19.1 (K)
unnamed: Z14.1 (K), Z20.1 (K)
unnamed: Z15.1 (K), Z21.1 (K)
unnamed: Z16.1 (K), Z22.1 (K)
unnamed: Z17.1 (K), Z23.1 (K)
unnamed: Z18.1 (K), Z24.1 (K)
TONE 1: J1.A21, U13.6
TONE 2: J1.A23, U13.4
TONE 3: J1.A25, U13.2
TONE 4: J1.A27, U13.12
TONE 5: J1.A29, U13.10
TONE 6: J1.A31, U13.8
TONE 7: J1.B21, U14.8
TONE 8: J1.B23, U14.10
TONE 9: J1.B25, U14.12
TONE 10: J1.B27, U14.2
TONE 11: J1.B29, U14.4
TONE 12: J1.B31, U14.6

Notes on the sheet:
C Note Oscillator
F# Note Oscillator
B Note Oscillator
A# Note Oscillator
C# Note Oscillator
A Note Oscillator
E Note Oscillator
Edge Connector
D Note Oscillator
G Note Oscillator
F Note Oscillator
D# Note Oscillator
G# Note Oscillator
